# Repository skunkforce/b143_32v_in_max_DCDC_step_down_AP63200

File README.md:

# edgy_board number b143
This design is part of the [edgy board project](https://github.com/skunkforce/edgy_boards). It provides a 2A step down DCDC converter. 

# getting started
This repository uses submodules. After cloning use the command 

```$ git submodule update --init --recursive```

to pull the submodules before opening the project with kicad. 

# Tests
Tests can be found in [TESTS.md](TESTS.md)

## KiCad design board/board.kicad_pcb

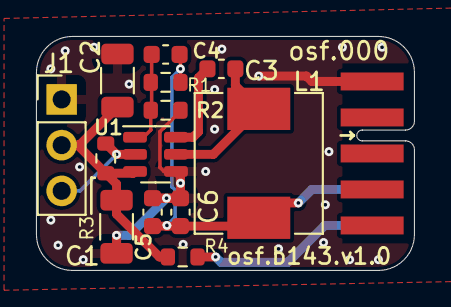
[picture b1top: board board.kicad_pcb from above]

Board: 2 copper layers, 21.0 x 13.0 mm, 15 parts (1 on the bottom side), 8 nets.

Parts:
C1: 10uF; C_1206_3216Metric
C2: 2.2uF; C_1206_3216Metric
C3: 100nF; C_0603_1608Metric
C4: d.n.p; C_0603_1608Metric
C5, C6: 22uF; C_0603_1608Metric
J1: Conn_01x03_Male; PinHeader_1x03_P2.54mm_Vertical
J2: 003_power; on_edge_2x05_host
L1: 6.8uH; L_Chilisin_BMRB00060612
LOGO1: Logo_Open_Hardware_Small; OSHW-Symbol_6.7x6mm_SilkScreen
R1: 182k; R_0603_1608Metric
R2: 62k; R_0603_1608Metric
R3, R4: 0R; R_0603_1608Metric
U1: AP63200WU; TSOT-23-6

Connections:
/step_down/EN: J1.3, R3.1, U1.2 (EN)
/step_down/FB: C4.2, R1.2, R2.1, U1.1 (FB)
/step_down/SW: C3.1, L1.1, U1.5 (SW)
/step_down/in: C1.1, C2.1, J1.2, R3.2, R4.1, U1.3 (IN)
/step_down/out: C4.1, C5.1, C6.1, J2.9 (3.3V), L1.2, R1.1
GND: C1.2, C2.2, C5.2, C6.2, J1.1, J2.1 (GND), R2.2, U1.4 (GND)
unnamed: J2.10 (5V), R4.2
unnamed: C3.2, U1.6 (BST)

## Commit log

2023-12-05 initial
2023-12-05 fixed README
